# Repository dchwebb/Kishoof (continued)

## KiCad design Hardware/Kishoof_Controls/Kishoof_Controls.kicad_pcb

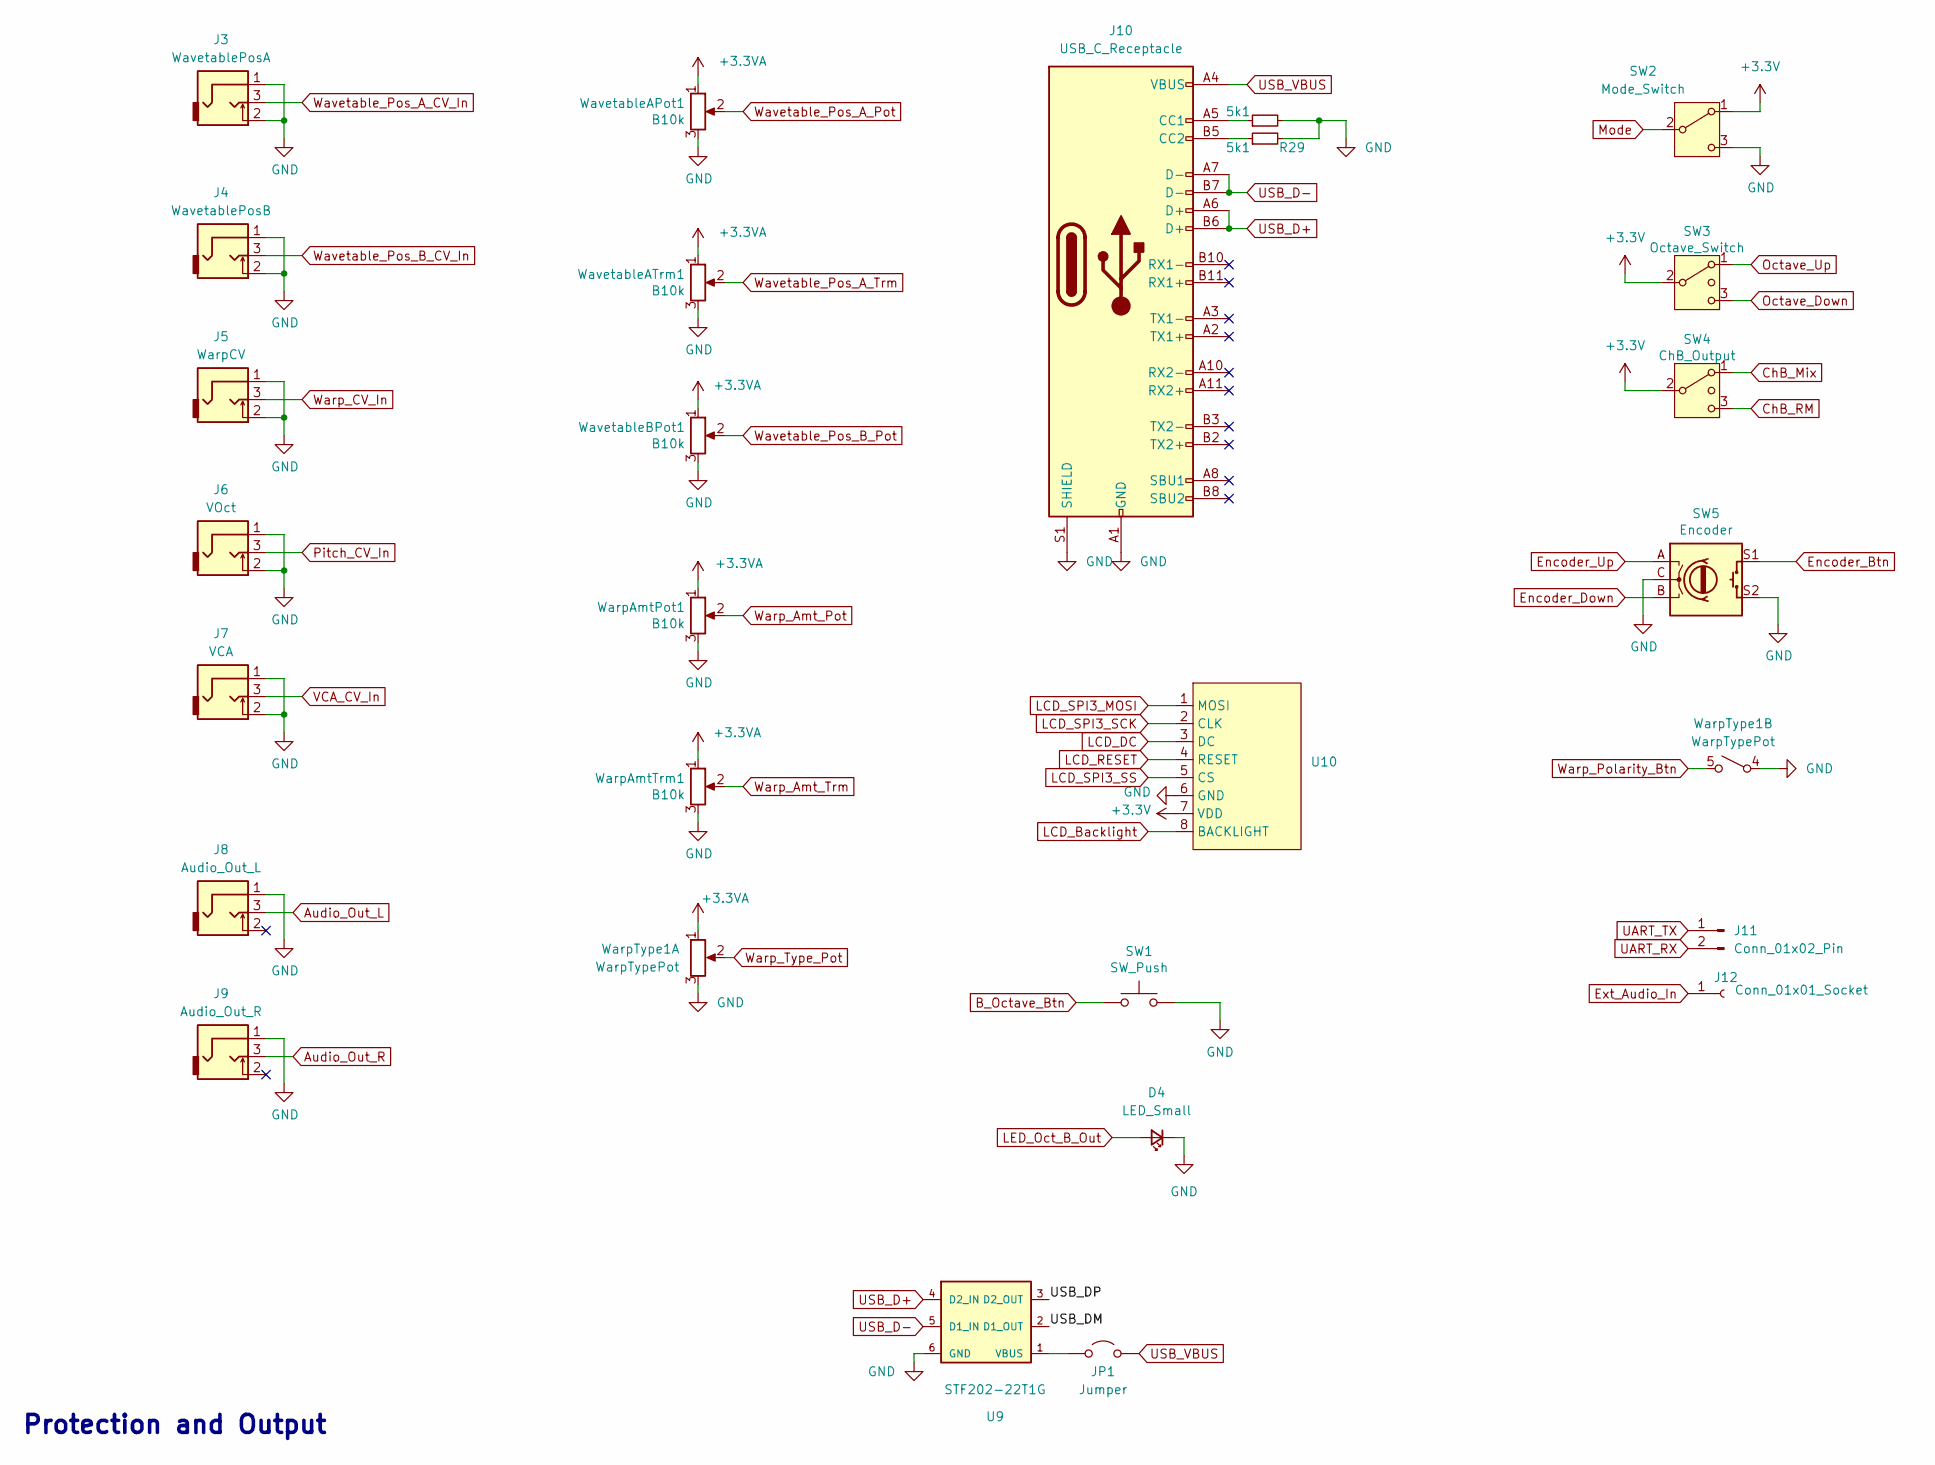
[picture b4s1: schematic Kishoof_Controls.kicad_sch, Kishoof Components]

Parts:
D4: LED_Small; LED_D3.0mm_FlatTop
J3: WavetablePosA; THONKICONN_hole
J4: WavetablePosB; THONKICONN_hole
J5: WarpCV; THONKICONN_hole
J6: VOct; THONKICONN_hole
J7: VCA; THONKICONN_hole
J8: Audio_Out_L; THONKICONN_hole
J9: Audio_Out_R; THONKICONN_hole
J10: USB_C_Receptacle; USB_C_Receptacle_Amphenol_12401951E412A
J11: Conn_01x02_Pin; PinHeader_1x02_P2.54mm_Vertical
J12: Conn_01x01_Socket; PinHeader_1x01_P2.54mm_Vertical
JP1: Jumper; SolderJumper-2_P1.3mm_Open_RoundedPad1.0x1.5mm
R28, R29: 5k1; R_0603_1608Metric; Part_Number C23186
SW1: SW_Push; SW_PUSH_6mm_aligned
SW2: Mode_Switch; SPDT_Miniature
SW3: Octave_Switch; SP3T_Mini_Switch
SW4: ChB_Output; SP3T_Mini_Switch
SW5: Encoder
U9: STF202-22T1G
U10: LCD_Riser
WarpAmtPot1: B10k; Alpha_9mm_Potentiometer_Aligned
WarpAmtTrm1: B10k; Alpha_9mm_Potentiometer_Aligned
WarpType1: WarpTypePot; Bourns_Switch_Potentiometer
WavetableAPot1: B10k; Alpha_9mm_Potentiometer_Aligned
WavetableATrm1: B10k; Alpha_9mm_Potentiometer_Aligned
WavetableBPot1: B10k; Alpha_9mm_Potentiometer_Aligned

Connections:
+3.3V: SW2.1 (A), SW3.2 (3), SW4.2 (3), U10.7 (VDD)
+3.3VA: WarpAmtPot1.1, WarpAmtTrm1.1, WarpType1.1, WavetableAPot1.1, WavetableATrm1.1, WavetableBPot1.1
/USB_DM: U9.2 (D1_OUT)
/USB_DP: U9.3 (D2_OUT)
Audio_Out_L: J8.3
Audio_Out_R: J9.3
B_Octave_Btn: SW1.1
ChB_Mix: SW4.1
ChB_RM: SW4.3 (4)
Encoder_Btn: SW5.S1
Encoder_Down: SW5.B
Encoder_Up: SW5.A
Ext_Audio_In: J12.1
GND: D4.1 (K), J3.1, J3.2, J4.1, J4.2, J5.1, J5.2, J6.1, J6.2, J7.1, J7.2, J8.1, J9.1, J10.A1 (GND), J10.A12 (GND), J10.B1 (GND), J10.B12 (GND), J10.S1 (SHIELD), R28.2, R29.2, SW1.2, SW2.3 (C), SW5.C, SW5.S2, U9.6 (GND), U10.6 (GND), WarpAmtPot1.3, WarpAmtTrm1.3, WarpType1.3, WarpType1.4 (1), WavetableAPot1.3, WavetableATrm1.3, WavetableBPot1.3
LCD_Backlight: U10.8 (BACKLIGHT)
LCD_DC: U10.3 (DC)
LCD_RESET: U10.4 (RESET)
LCD_SPI3_MOSI: U10.1 (MOSI)
LCD_SPI3_SCK: U10.2 (CLK)
LCD_SPI3_SS: U10.5 (CS)
LED_Oct_B_Out: D4.2 (A)
Mode: SW2.2 (B)
unnamed: J10.A5 (CC1), R28.1
unnamed: J10.B5 (CC2), R29.1
unnamed: JP1.1 (A), U9.1 (VBUS)
Octave_Down: SW3.3 (4)
Octave_Up: SW3.1
Pitch_CV_In: J6.3
UART_RX: J11.2
UART_TX: J11.1
USB_D+: J10.A6 (D+), J10.B6 (D+), U9.4 (D2_IN)
USB_D-: J10.A7 (D-), J10.B7 (D-), U9.5 (D1_IN)
USB_VBUS: J10.A4 (VBUS), J10.A9 (VBUS), J10.B4 (VBUS), J10.B9 (VBUS), JP1.2 (B)
VCA_CV_In: J7.3
Warp_Amt_Pot: WarpAmtPot1.2
Warp_Amt_Trm: WarpAmtTrm1.2
Warp_CV_In: J5.3
Warp_Polarity_Btn: WarpType1.5 (2)
Warp_Type_Pot: WarpType1.2
Wavetable_Pos_A_CV_In: J3.3
Wavetable_Pos_A_Pot: WavetableAPot1.2
Wavetable_Pos_A_Trm: WavetableATrm1.2
Wavetable_Pos_B_CV_In: J4.3
Wavetable_Pos_B_Pot: WavetableBPot1.2

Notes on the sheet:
Protection and Output

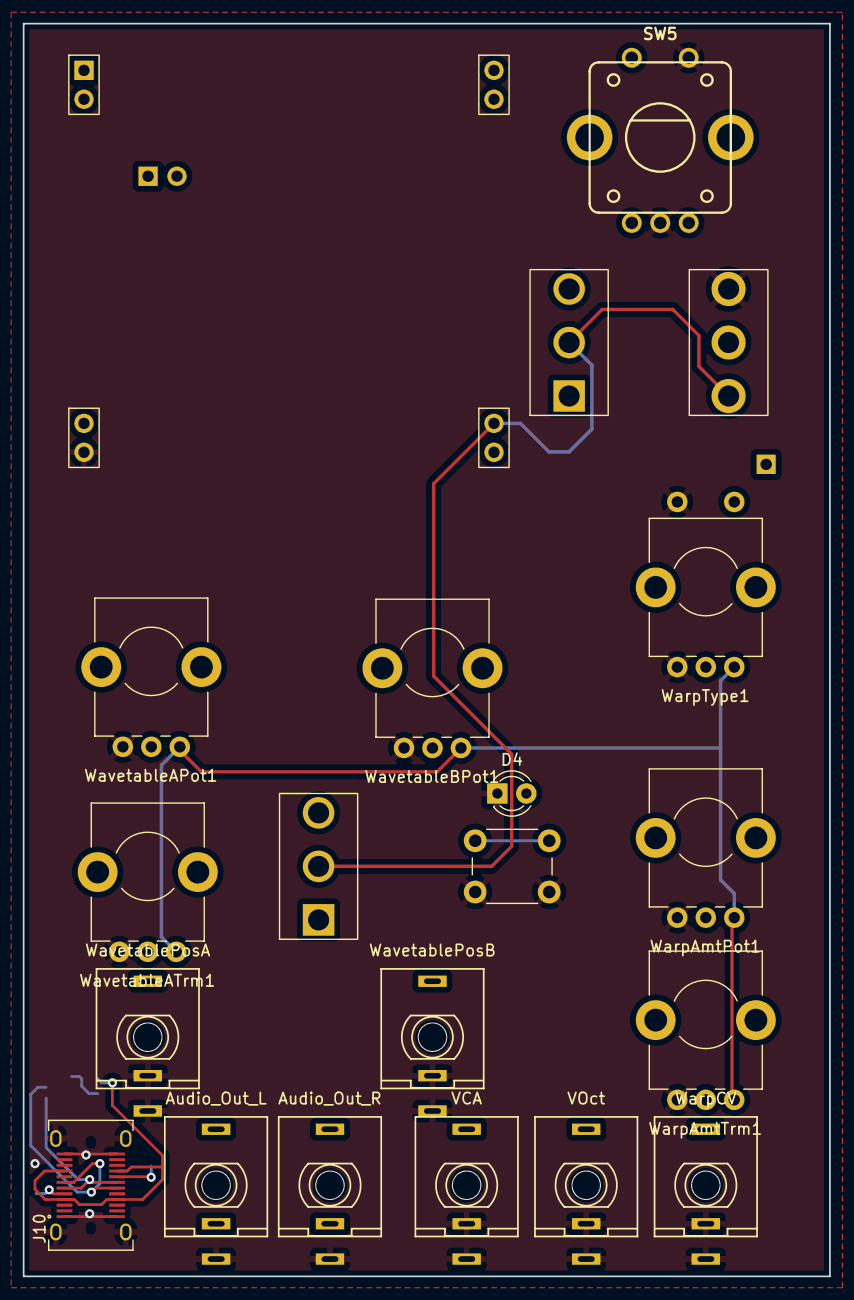
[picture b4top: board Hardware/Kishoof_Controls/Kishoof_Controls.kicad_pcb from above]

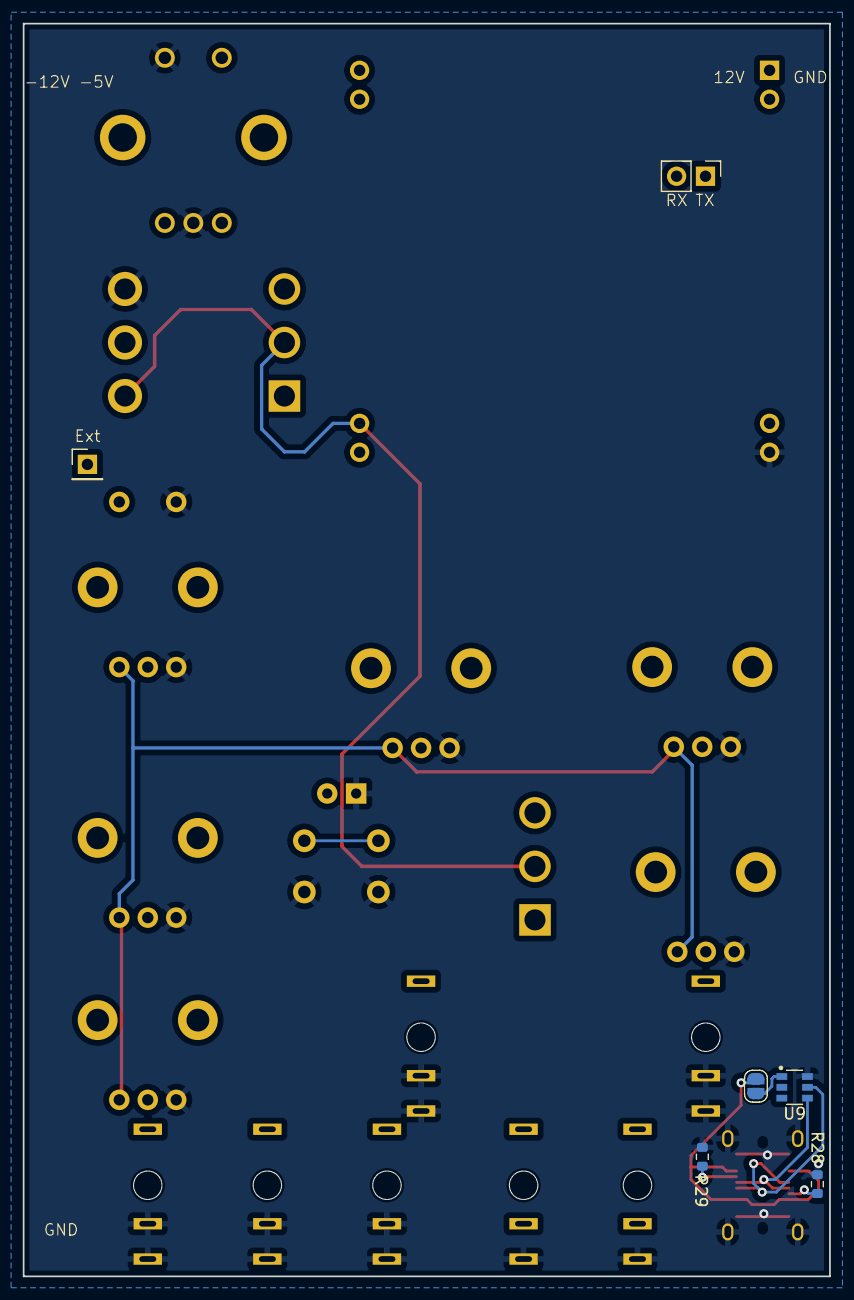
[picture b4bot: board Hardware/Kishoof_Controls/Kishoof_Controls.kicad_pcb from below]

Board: 4 copper layers, 70.8 x 110.0 mm, 27 parts (6 on the bottom side), 9 nets.

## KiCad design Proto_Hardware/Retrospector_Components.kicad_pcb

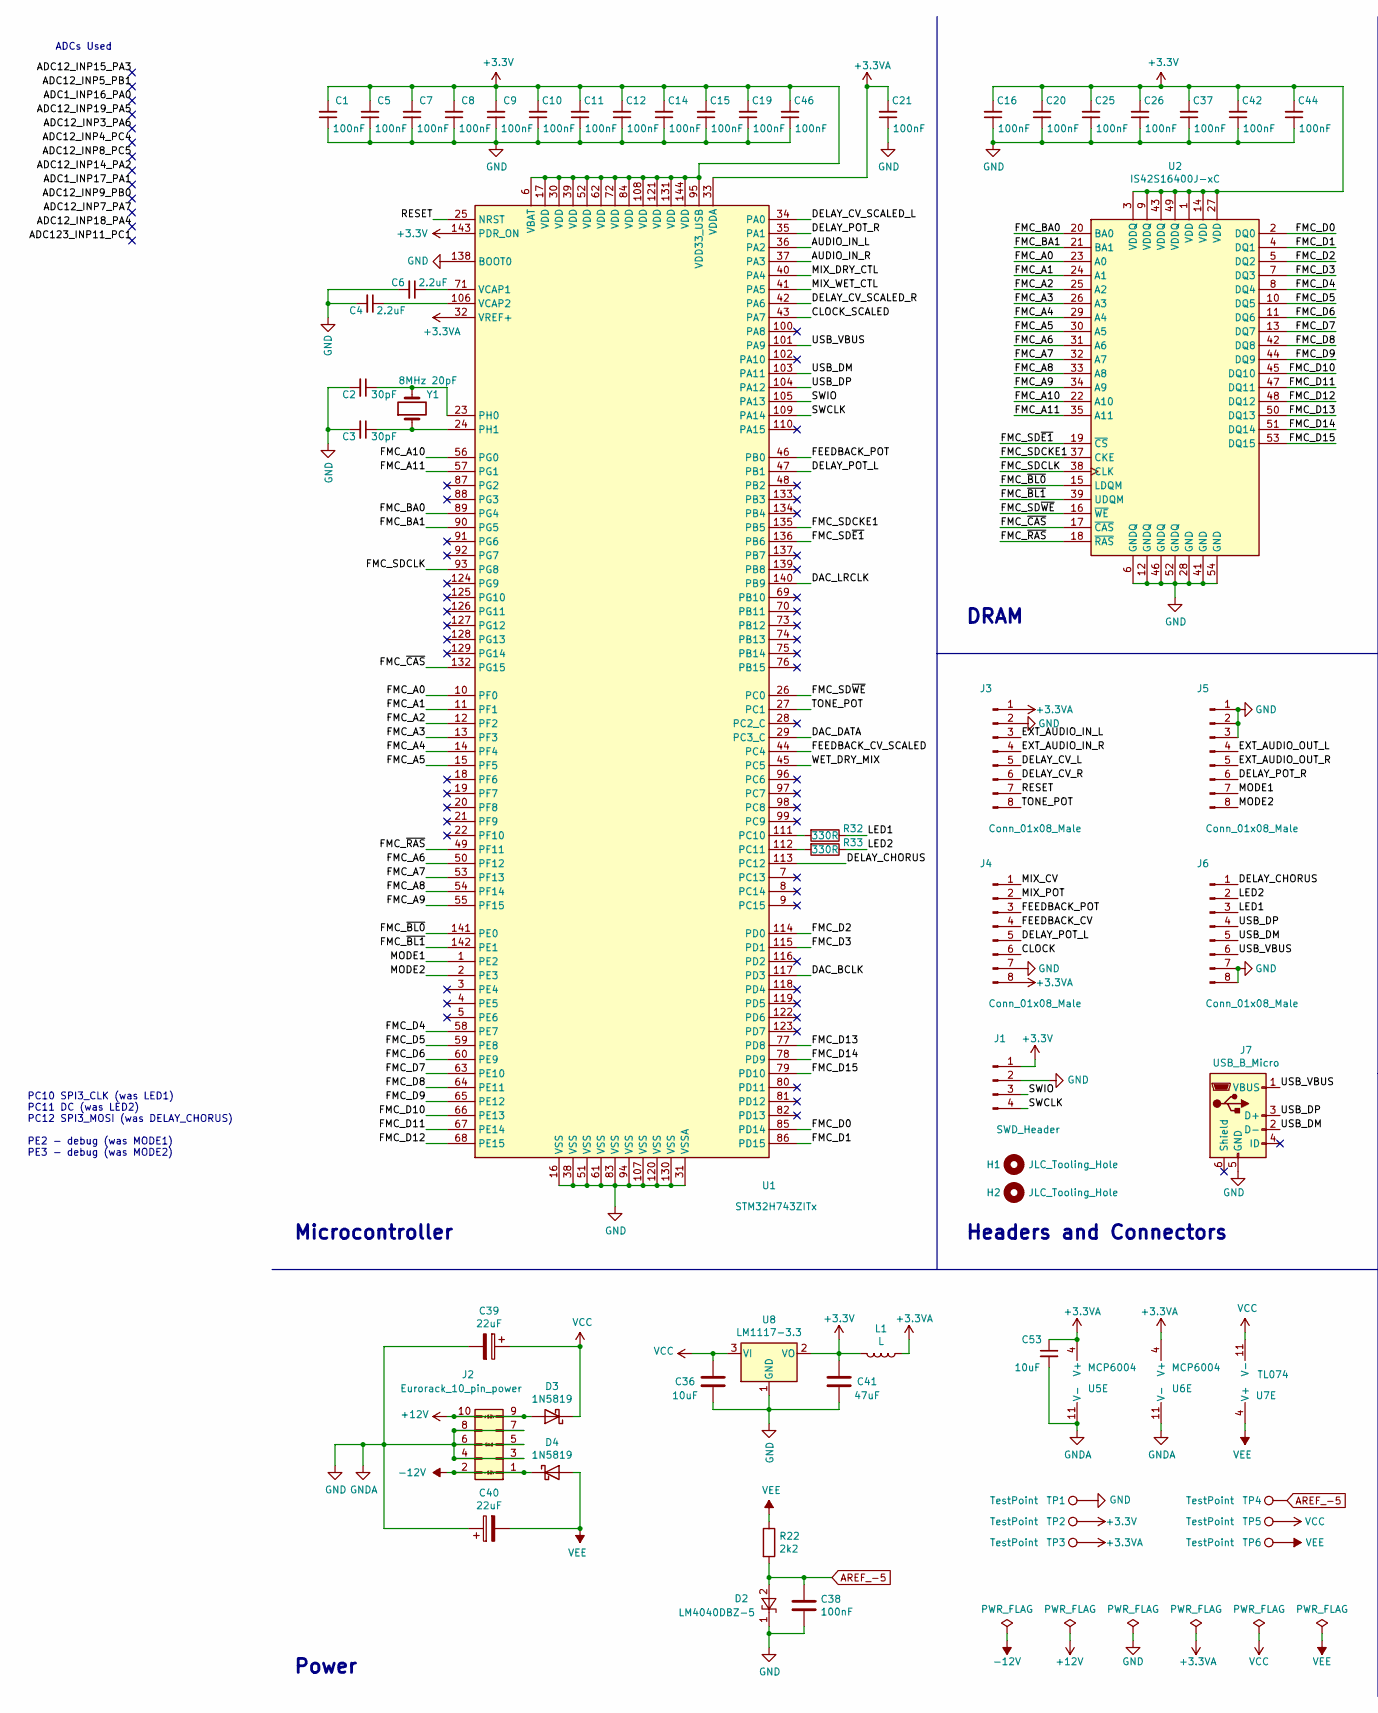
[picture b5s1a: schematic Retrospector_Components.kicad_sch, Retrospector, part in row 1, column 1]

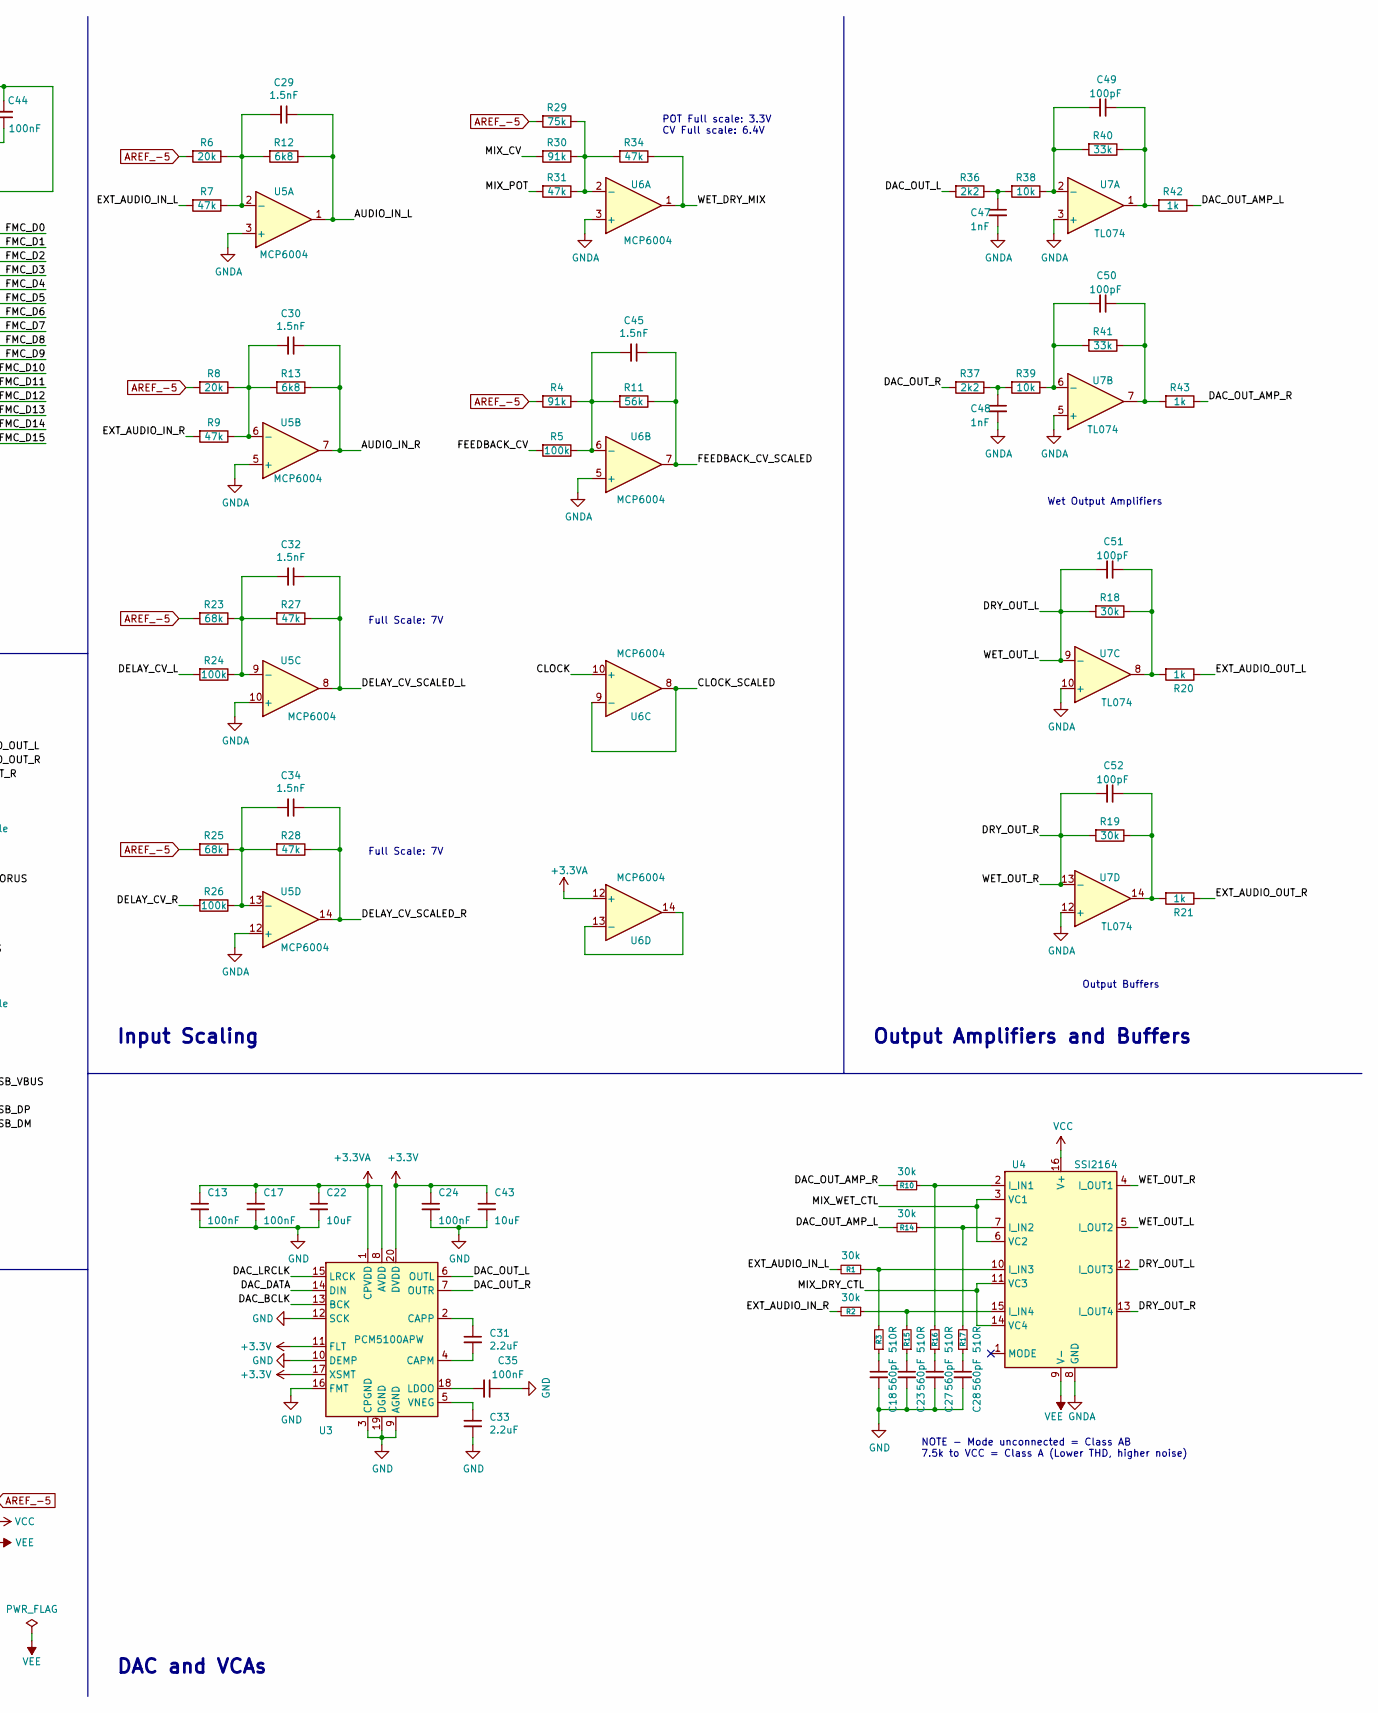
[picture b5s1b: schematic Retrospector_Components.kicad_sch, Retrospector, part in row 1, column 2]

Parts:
C1, C5, C7, C8, C9, C10, C11, C12, C13, C14, C15, C16, C17, C19, C20, C21, C24, C25, C26, C35, C37, C38, C42, C44, C46: 100nF; C_0603_HandSoldering; Part_Number C14663
C2, C3: 30pF; C_0603_HandSoldering; Part_Number C22397
C4, C6, C31, C33: 2.2uF; C_0603_HandSoldering; Part_Number C23630
C18, C23, C27, C28: 560pF; C_0603_HandSoldering; Part_Number C84721
C22, C43, C53: 10uF; C_0805; Part_Number C15850
C29, C30, C32, C34, C45: 1.5nF; C_0603_HandSoldering; Part_Number C1595
C36: 10uF; CP_Elec_3x5.3; Part_Number C249452
C39, C40: 22uF; CP_Elec_6.3x5.3; Part_Number C249771
C41: 47uF; CP_Elec_6.3x7.7; Part_Number C108053
C47, C48: 1nF; C_0805; Part_Number C46653
C49, C50, C51, C52: 100pF; C_0805; Part_Number C1790
D2: LM4040DBZ-5; SOT-23; Part_Number C69316
D3, D4: 1N5819; D_SOD-123; Part_Number C169540
H1, H2: JLC_Tooling_Hole; JLC_SMT_Tooling_Hole
J1: SWD_Header; SWD_header
J2: Eurorack_10_pin_power; Eurorack_10_pin_header
J3, J4, J5, J6: Conn_01x08_Male; Pin_Header_Straight_1x08_Pitch2.54mm
J7: USB_B_Micro; USB_Micro-B_Amphenol
L1: L; L_0805_HandSoldering; Part_Number C1046
R1, R2, R10, R14, R18, R19: 30k; R_0603_HandSoldering; Part_Number C22984
R3, R15, R16, R17: 510R; R_0603_HandSoldering; Part_Number C23193
R4, R30: 91k; R_0603_HandSoldering; Part_Number C23265
R5, R24, R26: 100k; R_0603_HandSoldering; Part_Number C25803
R6, R8: 20k; R_0603_HandSoldering; Part_Number C4184
R7, R9, R27, R28, R31, R34: 47k; R_0603_HandSoldering; Part_Number C25819
R11: 56k; R_0603_HandSoldering; Part_Number C23206
R12, R13: 6k8; R_0603_HandSoldering; Part_Number C23212
R20, R21, R42, R43: 1k; R_0603_HandSoldering; Part_Number C21190
R22, R36, R37: 2k2; R_0603_HandSoldering; Part_Number C4190
R23, R25: 68k; R_0603_HandSoldering; Part_Number C23231
R29: 75k; R_0603_HandSoldering; Part_Number C23242
R32, R33: 330R; R_0603_HandSoldering; Part_Number C23138
R38, R39: 10k; R_0603_HandSoldering; Part_Number C25804
R40, R41: 33k; R_0603_HandSoldering; Part_Number C4216
TP1, TP2, TP3, TP4, TP5, TP6: TestPoint; Test_Point_Keystone_5005-5009_Compact
U1: STM32H743ZITx; LQFP-144_20x20mm_P0.5mm; Part_Number C114408
U2: IS42S16400J-xC; TSOP-II-54_22.2x10.16mm_P0.8mm; Part_Number C69411
U3: PCM5100APW; SSOP-20_4.4x6.5mm_Pitch0.65mm_Round_Pads; Part_Number C131154
U4: SSI2164; SOIC-16_3.9x9.9mm_Pitch1.27mm
U5, U6: MCP6004; SOIC-14_N; Part_Number C7378
U7: TL074; SOIC-14_N; Part_Number C6964
U8: LM1117-3.3; SOT-223; Part_Number C6186
Y1: 8MHz 20pF; Crystal_SMD_5032-2pin_5.0x3.2mm_HandSoldering; Part_Number C115962

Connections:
+3.3VA: C13.1, C17.1, C21.2, C22.1, C53.1, J3.1, J4.8, L1.1, TP3.1, U1.32 (VREF+), U1.33 (VDDA), U3.1 (CPVDD), U3.8 (AVDD), U5.4 (V+), U6.4 (V+), U6.12 (+)
+3V3: C1.2, C5.2, C7.2, C8.2, C9.2, C10.2, C11.2, C12.2, C14.2, C15.2, C16.2, C19.2, C20.2, C24.1, C25.2, C26.2, C37.2, C41.1, C42.2, C43.1, C44.2, C46.2, J1.1, L1.2, TP2.1, U1.6 (VBAT), U1.17 (VDD), U1.30 (VDD), U1.39 (VDD), U1.52 (VDD), U1.62 (VDD), U1.72 (VDD), U1.84 (VDD), U1.95 (VDD33_USB), U1.108 (VDD), U1.121 (VDD), U1.131 (VDD), U1.143 (PDR_ON), U1.144 (VDD), U2.1 (VDD), U2.3 (VDDQ), U2.9 (VDDQ), U2.14 (VDD), U2.27 (VDD), U2.43 (VDDQ), U2.49 (VDDQ), U3.11 (FLT), U3.17 (XSMT), U3.20 (DVDD), U8.2 (VO)
+12V: D3.2 (A), J2.9, J2.10
-12V: D4.1 (K), J2.1, J2.2
/AUDIO_IN_L: C29.1, R12.1, U1.36 (PA2), U5.1
/AUDIO_IN_R: C30.1, R13.1, U1.37 (PA3), U5.7
/CLOCK: J4.6, U6.10 (+)
/CLOCK_SCALED: U1.43 (PA7), U6.8, U6.9 (-)
/DAC_BCLK: U1.117 (PD3), U3.13 (BCK)
/DAC_DATA: U1.29 (PC3_C), U3.14 (DIN)
/DAC_LRCLK: U1.140 (PB9), U3.15 (LRCK)
/DAC_OUT_AMP_L: R14.2, R42.1
/DAC_OUT_AMP_R: R10.2, R43.1
/DAC_OUT_L: R36.2, U3.6 (OUTL)
/DAC_OUT_R: R37.2, U3.7 (OUTR)
/DELAY_CHORUS: J6.1, U1.113 (PC12)
/DELAY_CV_L: J3.5, R24.2
/DELAY_CV_R: J3.6, R26.2
/DELAY_CV_SCALED_L: C32.1, R27.1, U1.34 (PA0), U5.8
/DELAY_CV_SCALED_R: C34.1, R28.1, U1.42 (PA6), U5.14
/DELAY_POT_L: J4.5, U1.47 (PB1)
/DELAY_POT_R: J5.6, U1.35 (PA1)
/DRY_OUT_L: C51.2, R18.2, U4.5 (I_OUT2), U4.12 (I_OUT3), U7.9 (-)
/DRY_OUT_R: C52.2, R19.2, U4.4 (I_OUT1), U4.13 (I_OUT4), U7.13 (-)
/EXT_AUDIO_IN_L: J3.3, R1.2, R7.2
/EXT_AUDIO_IN_R: J3.4, R2.2, R9.2
/EXT_AUDIO_OUT_L: J5.4, R20.1
/EXT_AUDIO_OUT_R: J5.5, R21.1
/FEEDBACK_CV: J4.4, R5.2
/FEEDBACK_CV_SCALED: C45.1, R11.1, U1.44 (PC4), U6.7
/FEEDBACK_POT: J4.3, U1.46 (PB0)
/FMC_A0: U1.10 (PF0), U2.23 (A0)
/FMC_A1: U1.11 (PF1), U2.24 (A1)
/FMC_A2: U1.12 (PF2), U2.25 (A2)
/FMC_A3: U1.13 (PF3), U2.26 (A3)
/FMC_A4: U1.14 (PF4), U2.29 (A4)
/FMC_A5: U1.15 (PF5), U2.30 (A5)
/FMC_A6: U1.50 (PF12), U2.31 (A6)
/FMC_A7: U1.53 (PF13), U2.32 (A7)
/FMC_A8: U1.54 (PF14), U2.33 (A8)
/FMC_A9: U1.55 (PF15), U2.34 (A9)
/FMC_A10: U1.56 (PG0), U2.22 (A10)
/FMC_A11: U1.57 (PG1), U2.35 (A11)
/FMC_BA0: U1.89 (PG4), U2.20 (BA0)
/FMC_BA1: U1.90 (PG5), U2.21 (BA1)
/FMC_D0: U1.85 (PD14), U2.2 (DQ0)
/FMC_D1: U1.86 (PD15), U2.4 (DQ1)
/FMC_D2: U1.114 (PD0), U2.5 (DQ2)
/FMC_D3: U1.115 (PD1), U2.7 (DQ3)
/FMC_D4: U1.58 (PE7), U2.8 (DQ4)
/FMC_D5: U1.59 (PE8), U2.10 (DQ5)
/FMC_D6: U1.60 (PE9), U2.11 (DQ6)
/FMC_D7: U1.63 (PE10), U2.13 (DQ7)
/FMC_D8: U1.64 (PE11), U2.42 (DQ8)
/FMC_D9: U1.65 (PE12), U2.44 (DQ9)
/FMC_D10: U1.66 (PE13), U2.45 (DQ10)
/FMC_D11: U1.67 (PE14), U2.47 (DQ11)
/FMC_D12: U1.68 (PE15), U2.48 (DQ12)
/FMC_D13: U1.77 (PD8), U2.50 (DQ13)
/FMC_D14: U1.78 (PD9), U2.51 (DQ14)
/FMC_D15: U1.79 (PD10), U2.53 (DQ15)
/FMC_SDCKE1: U1.135 (PB5), U2.37 (CKE)
/FMC_SDCLK: U1.93 (PG8), U2.38 (CLK)
/FMC_SD~E1: U1.136 (PB6), U2.19 (~CS)
/FMC_SD~WE: U1.26 (PC0), U2.16 (~WE)
/FMC_~BL0: U1.141 (PE0), U2.15 (LDQM)
/FMC_~BL1: U1.142 (PE1), U2.39 (UDQM)
/FMC_~CAS: U1.132 (PG15), U2.17 (~CAS)
/FMC_~RAS: U1.49 (PF11), U2.18 (~RAS)
/LED1: J6.3, R32.1
/LED2: J6.2, R33.1
/MIX_CV: J4.1, R30.2
/MIX_DRY_CTL: U1.40 (PA4), U4.11 (VC3), U4.14 (VC4)
/MIX_POT: J4.2, R31.2
/MIX_WET_CTL: U1.41 (PA5), U4.3 (VC1), U4.6 (VC2)
/MODE1: J5.7, U1.1 (PE2)
/MODE2: J5.8, U1.2 (PE3)
/RESET: J3.7, U1.25 (NRST)
/SWCLK: J1.4, U1.109 (PA14)
/SWIO: J1.3, U1.105 (PA13)
/TONE_POT: J3.8, U1.27 (PC1)
/USB_DM: J6.5, J7.2 (D-), U1.103 (PA11)
/USB_DP: J6.4, J7.3 (D+), U1.104 (PA12)
/USB_VBUS: J6.6, J7.1 (VBUS), U1.101 (PA9)
/WET_DRY_MIX: R34.1, U1.45 (PC5), U6.1
AREF_-5: C38.1, D2.2 (A), R4.2, R6.2, R8.2, R22.2, R23.2, R25.2, R29.2, TP4.1
GND: C1.1, C2.2, C3.2, C4.2, C5.1, C6.2, C7.1, C8.1, C9.1, C10.1, C11.1, C12.1, C13.2, C14.1, C15.1, C16.1, C17.2, C18.2, C19.1, C20.1, C21.1, C22.2, C23.2, C24.2, C25.1, C26.1, C27.2, C28.2, C33.2, C35.1, C36.2, C37.1, C38.2, C39.2, C40.1, C41.2, C42.1, C43.2, C44.1, C46.1, C47.2, C48.2, C53.2, D2.1 (K), J1.2, J2.3, J2.4, J2.5, J2.6, J2.7, J2.8, J3.2, J4.7, J5.1, J5.2, J5.3, J6.7, J6.8, J7.5 (GND), TP1.1, U1.16 (VSS), U1.31 (VSSA), U1.38 (VSS), U1.51 (VSS), U1.61 (VSS), U1.83 (VSS), U1.94 (VSS), U1.107 (VSS), U1.120 (VSS), U1.130 (VSS), U1.138 (BOOT0), U2.6 (GNDQ), U2.12 (GNDQ), U2.28 (GND), U2.41 (GND), U2.46 (GNDQ), U2.52 (GNDQ), U2.54 (GND), U3.3 (CPGND), U3.9 (AGND)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
unnamed: C2.1, U1.23 (PH0), Y1.2
unnamed: C3.1, U1.24 (PH1), Y1.1
unnamed: C4.1, U1.106 (VCAP2)
unnamed: C6.1, U1.71 (VCAP1)
unnamed: C18.1, R3.1
unnamed: C23.1, R15.1
unnamed: C27.1, R16.1
unnamed: C28.1, R17.1
unnamed: C29.2, R6.1, R7.1, R12.2, U5.2 (-)
unnamed: C30.2, R8.1, R9.1, R13.2, U5.6 (-)
unnamed: C31.1, U3.2 (CAPP)
unnamed: C31.2, U3.4 (CAPM)
unnamed: C32.2, R23.1, R24.1, R27.2, U5.9 (-)
unnamed: C33.1, U3.5 (VNEG)
unnamed: C34.2, R25.1, R26.1, R28.2, U5.13 (-)
unnamed: C35.2, U3.18 (LDOO)
unnamed: C45.2, R4.1, R5.1, R11.2, U6.6 (-)
unnamed: C47.1, R36.1, R38.2
unnamed: C48.1, R37.1, R39.2
unnamed: C49.1, R40.1, R42.2, U7.1
unnamed: C49.2, R38.1, R40.2, U7.2 (-)
unnamed: C50.1, R41.1, R43.2, U7.7
unnamed: C50.2, R39.1, R41.2, U7.6 (-)
unnamed: C51.1, R18.1, R20.2, U7.8
unnamed: C52.1, R19.1, R21.2, U7.14
unnamed: R1.1, R3.2, U4.10 (I_IN3)
unnamed: R10.1, R16.2, U4.2 (I_IN1)
unnamed: R14.1, R17.2, U4.7 (I_IN2)
unnamed: R2.1, R15.2, U4.15 (I_IN4)
unnamed: R29.1, R30.1, R31.1, R34.2, U6.2 (-)
unnamed: R32.2, U1.111 (PC10)
unnamed: R33.2, U1.112 (PC11)
unnamed: U6.13 (-), U6.14
VCC: C36.1, C39.1, D3.1 (K), TP5.1, U4.16 (V+), U7.11 (V-), U8.3 (VI)
VEE: C40.2, D4.2 (A), R22.1, TP6.1, U4.9 (V-), U7.4 (V+)

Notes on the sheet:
DAC and VCAs
NOTE - Mode unconnected = Class AB 7.5k to VCC = Class A (Lower THD, higher noise)
Input Scaling
Output Buffers
ADCs Used
Full Scale: 7V
Wet Output Amplifiers
Output Amplifiers and Buffers
POT Full scale: 3.3V CV Full scale: 6.4V
Power
PC10 SPI3_CLK (was LED1) PC11 DC (was LED2) PC12 SPI3_MOSI (was DELAY_CHORUS) PE2 - debug (was MODE1) PE3 - debug (was MODE2)
Microcontroller
Headers and Connectors
DRAM

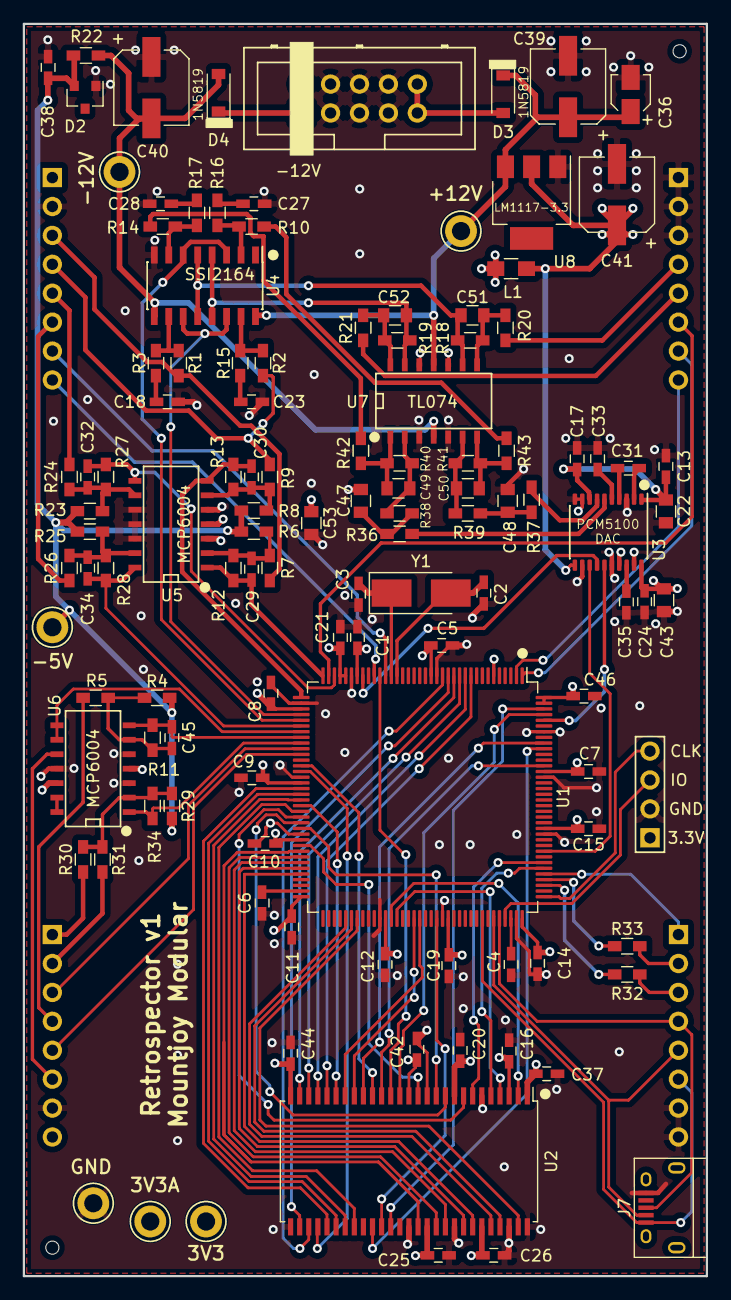
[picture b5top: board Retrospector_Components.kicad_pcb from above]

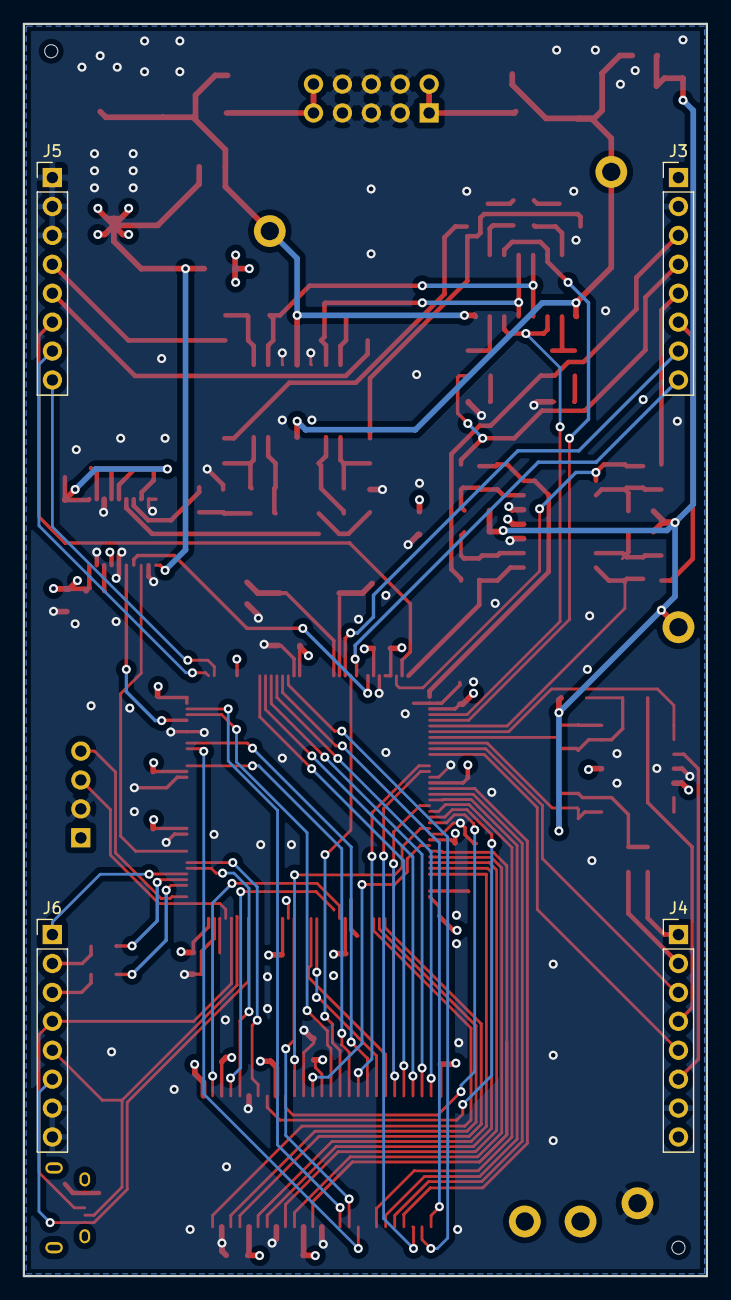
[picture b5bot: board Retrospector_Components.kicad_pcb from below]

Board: 4 copper layers, 60.0 x 110.0 mm, 123 parts (4 on the bottom side), 122 nets.

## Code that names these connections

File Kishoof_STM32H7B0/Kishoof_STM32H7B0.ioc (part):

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Mcu.Name=STM32H7B0VBTx
Mcu.Package=LQFP100
Mcu.UserName=STM32H7B0VBTx
PA0.Mode=IN16-Single-Ended
PA0.Signal=ADC1_INP16
PA1.Mode=IN17-Single-Ended
PA1.Signal=ADC1_INP17
PA11.Mode=Host_FS
PA11.Signal=USB_OTG_HS_DM
PA12.Mode=Host_FS
PA12.Signal=USB_OTG_HS_DP
PA15.Mode=NSS_Signal_Hard_Output
PA15.Signal=SPI3_NSS
PA2.Signal=ADCx_INP14
PA3.Mode=IN15-Single-Ended
PA3.Signal=ADC1_INP15
PA4.Signal=ADCx_INP18
PA5.Signal=ADCx_INP19
PA6.Signal=ADCx_INP3
PA7.Signal=ADCx_INP7
PA9.Mode=Activate_VBUS_FS
PA9.Signal=USB_OTG_HS_VBUS
PB0.Signal=ADCx_INP9
PB1.Signal=ADCx_INP5
PB12.Mode=Half_Duplex_Master_Tx
PB12.Signal=I2S2_WS
PB13.Mode=Half_Duplex_Master_Tx
PB13.Signal=I2S2_CK
PB15.Mode=Half_Duplex_Master_Tx
PB15.Signal=I2S2_SDO
PB2.Mode=O1_P1_CLK
PB2.Signal=OCTOSPIM_P1_CLK
PB6.GPIOParameters=GPIO_Label
PB6.GPIO_Label=LCD_DC
PB6.Signal=GPIO_Input
PB7.GPIOParameters=GPIO_Label
PB7.GPIO_Label=LCD_RESET
PB7.Signal=GPIO_Input
PC0.Signal=ADCx_INP10
PC1.Signal=ADCx_INP11
PC10.Mode=TX_Only_Simplex_Unidirect_Master
PC10.Signal=SPI3_SCK
PC12.Mode=TX_Only_Simplex_Unidirect_Master
PC12.Signal=SPI3_MOSI
PC2_C.Mode=OCTOSPI1_IOL_Port1L
PC2_C.Signal=OCTOSPIM_P1_IO2
PC5.Mode=OCTOSPI1_Port1_DQS
PC5.Signal=OCTOSPIM_P1_DQS
PC6.Signal=S_TIM3_CH1
PC7.Signal=S_TIM3_CH2
PC9.Mode=OCTOSPI1_IOL_Port1L
PC9.Signal=OCTOSPIM_P1_IO0
PD0.GPIOParameters=GPIO_Label
PD0.GPIO_Label=Octave_Up
PD0.Signal=GPIO_Input
PD1.GPIOParameters=GPIO_Label
PD1.GPIO_Label=Octave_Down
PD1.Signal=GPIO_Input
PD10.GPIOParameters=GPIO_Label
PD10.GPIO_Label=B_Octave_Btn
PD10.Signal=GPIO_Input
PD12.Mode=OCTOSPI1_IOL_Port1L
PD12.Signal=OCTOSPIM_P1_IO1
PD13.Mode=OCTOSPI1_IOL_Port1L
PD13.Signal=OCTOSPIM_P1_IO3
PD14.Signal=S_TIM4_CH3
PD5.Mode=Asynchronous
PD5.Signal=USART2_TX
PD6.Mode=Asynchronous
PD6.Signal=USART2_RX
PD8.GPIOParameters=GPIO_Label
PD8.GPIO_Label=ChB_Mix
PD8.Signal=GPIO_Input
PD9.GPIOParameters=GPIO_Label
PD9.GPIO_Label=ChB_RM
PD9.Signal=GPIO_Input
PE10.Mode=OCTOSPI1_IOH_Port1H
PE10.Signal=OCTOSPIM_P1_IO7
PE11.Mode=OCTOSPI1_Port1_NCS
PE11.Signal=OCTOSPIM_P1_NCS
PE2.GPIOParameters=GPIO_Label
PE2.GPIO_Label=Mode
PE2.Signal=GPIO_Input
PE3.GPIOParameters=GPIO_Label
PE3.GPIO_Label=Warp_Polarity_Btn
PE3.Signal=GPIO_Input
PE4.GPIOParameters=GPIO_Label
PE4.GPIO_Label=ENCODER_BTN
PE4.Signal=GPIO_Input
PE7.Mode=OCTOSPI1_IOH_Port1H
PE7.Signal=OCTOSPIM_P1_IO4
PE8.Mode=OCTOSPI1_IOH_Port1H
PE8.Signal=OCTOSPIM_P1_IO5
PE9.Mode=OCTOSPI1_IOH_Port1H
PE9.Signal=OCTOSPIM_P1_IO6
PH0-OSC_IN.Mode=HSE-External-Oscillator
PH0-OSC_IN.Signal=RCC_OSC_IN
PH1-OSC_OUT.Mode=HSE-External-Oscillator
PH1-OSC_OUT.Signal=RCC_OSC_OUT
RCC.HSE_VALUE=8000000
RCC.SYSCLKFreq_VALUE=280000000
RCC.SYSCLKSource=RCC_SYSCLKSOURCE_PLLCLK
board=custom

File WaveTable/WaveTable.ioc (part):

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Mcu.Name=STM32H743ZITx
Mcu.Package=LQFP144
Mcu.UserName=STM32H743ZITx
PA11.Mode=Device_Only
PA11.Signal=USB_OTG_FS_DM
PA12.Mode=Device_Only
PA12.Signal=USB_OTG_FS_DP
PA4.Signal=ADCx_INP18
PA5.Signal=COMP_DAC12_group
PA7.Signal=FMC_SDNWE
PA8.Mode=Activate_SOF_FS
PA8.Signal=USB_OTG_FS_SOF
PA9.Mode=Activate_VBUS
PA9.Signal=USB_OTG_FS_VBUS
PB0.GPIOParameters=GPIO_Label
PB0.GPIO_Label=LD1 [Green Led]
PB0.Signal=GPIO_Output
PB13.Mode=Half_Duplex_Master_Tx
PB13.Signal=I2S2_CK
PB14.GPIOParameters=GPIO_Label
PB14.GPIO_Label=LD3 [Red Led]
PB14.Signal=GPIO_Output
PB15.Mode=Half_Duplex_Master_Tx
PB15.Signal=I2S2_SDO
PB5.Mode=SdramChipSelect2_2
PB5.Signal=FMC_SDCKE1
PB6.Mode=SdramChipSelect2_2
PB6.Signal=FMC_SDNE1
PB7.GPIOParameters=GPIO_Pu
PB7.GPIO_Pu=GPIO_PULLUP
PB7.Mode=I2C
PB7.Signal=I2C1_SDA
PB8.GPIOParameters=GPIO_Pu
PB8.GPIO_Pu=GPIO_PULLUP
PB8.Mode=I2C
PB8.Signal=I2C1_SCL
PB9.Mode=Half_Duplex_Master_Tx
PB9.Signal=I2S2_WS
PC0.Signal=ADCx_INP10
PC13.GPIOParameters=GPIO_Label
PC13.GPIO_Label=B1 [Blue PushButton]
PC13.Signal=GPIO_Input
PC14-OSC32_IN\ (OSC32_IN).Mode=LSE-External-Oscillator
PC14-OSC32_IN\ (OSC32_IN).Signal=RCC_OSC32_IN
PC15-OSC32_OUT\ (OSC32_OUT).Mode=LSE-External-Oscillator
PC15-OSC32_OUT\ (OSC32_OUT).Signal=RCC_OSC32_OUT
PD0.Signal=FMC_D2_DA2
PD1.Signal=FMC_D3_DA3
PD10.Signal=FMC_D15_DA15
PD14.Signal=FMC_D0_DA0
PD15.Signal=FMC_D1_DA1
PD8.Signal=FMC_D13_DA13
PD9.Signal=FMC_D14_DA14
PE0.Signal=FMC_NBL0
PE1.Signal=FMC_NBL1
PE10.Signal=FMC_D7_DA7
PE11.Signal=FMC_D8_DA8
PE12.Signal=FMC_D9_DA9
PE13.Signal=FMC_D10_DA10
PE14.Signal=FMC_D11_DA11
PE15.Signal=FMC_D12_DA12
PE7.Signal=FMC_D4_DA4
PE8.Signal=FMC_D5_DA5
PE9.Signal=FMC_D6_DA6
PF0.Signal=FMC_A0
PF1.Signal=FMC_A1
PF11.Signal=FMC_SDNRAS
PF12.Signal=FMC_A6
PF13.Signal=FMC_A7
PF14.Signal=FMC_A8
PF15.Signal=FMC_A9
PF2.Signal=FMC_A2
PF3.Signal=FMC_A3
PF4.Signal=FMC_A4
PF5.Signal=FMC_A5
PF7.Mode=TX_Only_Simplex_Unidirect_Master
PF7.Signal=SPI5_SCK
PF9.Mode=TX_Only_Simplex_Unidirect_Master
PF9.Signal=SPI5_MOSI
PG0.Signal=FMC_A10
PG1.Signal=FMC_A11
PG15.Signal=FMC_SDNCAS
PG2.Signal=FMC_A12
PG4.Signal=FMC_A14_BA0
PG5.Signal=FMC_A15_BA1
PG7.GPIOParameters=GPIO_Label
PG7.GPIO_Label=USB_OTG_FS_OVCR
PG7.Signal=GPXTI7
PG8.Signal=FMC_SDCLK
PH0-OSC_IN\ (PH0).Mode=HSE-External-Oscillator
PH0-OSC_IN\ (PH0).Signal=RCC_OSC_IN
PH1-OSC_OUT\ (PH1).Mode=HSE-External-Oscillator
PH1-OSC_OUT\ (PH1).Signal=RCC_OSC_OUT
RCC.HSE_VALUE=8000000
RCC.SYSCLKFreq_VALUE=400000000
RCC.SYSCLKSource=RCC_SYSCLKSOURCE_PLLCLK
board=NUCLEO-H743ZI2
boardIOC=true

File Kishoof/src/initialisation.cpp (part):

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#include "initialisation.h"
#include "Calib.h"

GpioPin debugPin1	{GPIOD, 6, GpioPin::Type::Output};			// PD5: Debug
GpioPin debugPin2	{GPIOD, 5, GpioPin::Type::Output};			// PD6: Debug

// Clock overview:
// I2S 				PLL2 P 				61.44 MHz
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	// Maximum frequency should be 100MHz - see GC9A01 manual p. 189
	RCC->APB1LENR |= RCC_APB1LENR_SPI3EN;

	GpioPin::Init(GPIOC, 10, GpioPin::Type::AlternateFunction, 6, GpioPin::DriveStrength::High);		// PC10: SPI3_SCK AF6
	GpioPin::Init(GPIOC, 12, GpioPin::Type::AlternateFunction, 6, GpioPin::DriveStrength::High);		// PC12: SPI3_MOSI AF6
	//GpioPin::Init(GPIOA, 15, GpioPin::Type::AlternateFunction, 6, GpioPin::DriveStrength::High);			// PA15: SPI3_SS AF6

	// Configure SPI
	SPI3->CFG2 |= SPI_CFG2_COMM_0;					// 00: full-duplex, *01: simplex transmitter, 10: simplex receiver, 11: half-duplex
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
/*-----------------------------------------------------------------------------------------------------------------
ADC1:
	PA0 ADC1_INP16 Wavetable_Pos_B_Pot
	PA1 ADC1_INP17 Wavetable_Pos_A_Trm
	PA2 ADC1_INP14 AudioIn
	PA3 ADC1_INP15 WarpCV
	PA4 ADC1_INP18 Pitch_CV_Scaled
	PA5 ADC1_INP19 WavetablePosB_CV
ADC2:
	PA6 ADC12_INP3 VcaCV
	PA7 ADC12_INP7 WavetablePosA_CV
	PB0 ADC12_INP9 Warp_Type_Pot
	PB1 ADC12_INP5 Wavetable_Pos_A_Pot
	PC0 ADC12_INP10 Warp_Amt_Trm
	PC1	ADC12_INP11	Warp_Amt_Pot
*/

void InitADC1()
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
	/*--------------------------------------------------------------------------------------------
	Configure ADC Channels to be converted:
	PA0 ADC1_INP16 Wavetable_Pos_B_Pot
	PA1 ADC1_INP17 Wavetable_Pos_A_Trm
	PA2 ADC1_INP14 AudioIn
	PA3 ADC1_INP15 WarpCV
	PA4 ADC1_INP18 Pitch_CV_Scaled
	PA5 ADC1_INP19 WavetablePosB_CV
	*/
	InitAdcPins(ADC1, {16, 17, 14, 15, 18, 19});

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	while ((ADC2->CR & ADC_CR_ADCAL) == ADC_CR_ADCAL) {};

	/* Configure ADC Channels to be converted:
	PA6 ADC12_INP3 VcaCV
	PA7 ADC12_INP7 WavetablePosA_CV
	PB0 ADC12_INP9 Warp_Type_Pot
	PB1 ADC12_INP5 Wavetable_Pos_A_Pot
	PC0 ADC12_INP10 Warp_Amt_Trm
	PC1	ADC12_INP11	Warp_Amt_Pot
	*/
	InitAdcPins(ADC2, {3, 7, 9, 5, 10, 11});

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{
	RCC->APB1LENR |= RCC_APB1LENR_SPI2EN;			//	Enable SPI clocks

	GpioPin::Init(GPIOB, 12, GpioPin::Type::AlternateFunction, 5);		// PB12: I2S2_WS [alternate function AF5]
	GpioPin::Init(GPIOB, 13, GpioPin::Type::AlternateFunction, 5);		// PB13: I2S2_CK [alternate function AF5]
	GpioPin::Init(GPIOB, 15, GpioPin::Type::AlternateFunction, 5);		// PB15: I2S2_SDO [alternate function AF5]

	// Configure SPI (Shown as SPI2->CGFR in SFR)
	SPI2->I2SCFGR |= SPI_I2SCFGR_I2SMOD;			// I2S Mode
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
void InitEncoders()
{
	// Encoder: button on PE4, up/down on PC6 and PC7
	GpioPin::Init(GPIOE, 4, GpioPin::Type::InputPullup);				// PE4: Button
	GpioPin::Init(GPIOC, 6, GpioPin::Type::AlternateFunction, 3);		// PC6: TIM8_CH1 AF3
	GpioPin::Init(GPIOC, 7, GpioPin::Type::AlternateFunction, 3);		// PC7: TIM8_CH2 AF3

	RCC->APB4ENR |= RCC_APB4ENR_SYSCFGEN;			// Enable system configuration clock: used to manage external interrupt line connection to GPIOs
	// Encoder using timer functionality - PC6 and PC7
	GPIOC->PUPDR |= GPIO_PUPDR_PUPD6_0 |			// Set encoder pins to pull up
					GPIO_PUPDR_PUPD7_0;

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
void InitOctoSPI()
{
	GpioPin::Init(GPIOB, 2, GpioPin::Type::AlternateFunction, 9, GpioPin::DriveStrength::VeryHigh);		// PB2  OCTOSPI_CLK AF9
	GpioPin::Init(GPIOC, 9, GpioPin::Type::AlternateFunction, 9, GpioPin::DriveStrength::VeryHigh);		// PC9  OCTOSPI_IO0 AF9
	GpioPin::Init(GPIOD, 12, GpioPin::Type::AlternateFunction, 9, GpioPin::DriveStrength::VeryHigh);	// PD12 OCTOSPI_IO1 AF9
	GpioPin::Init(GPIOC, 2, GpioPin::Type::AlternateFunction, 9, GpioPin::DriveStrength::VeryHigh);		// PC2  OCTOSPI_IO2 AF9
	GpioPin::Init(GPIOD, 13, GpioPin::Type::AlternateFunction, 9, GpioPin::DriveStrength::VeryHigh);	// PD13 OCTOSPI_IO3 AF9
	GpioPin::Init(GPIOE, 7, GpioPin::Type::AlternateFunction, 10, GpioPin::DriveStrength::VeryHigh); 	// PE7  OCTOSPI_IO4 AF10
	GpioPin::Init(GPIOE, 8, GpioPin::Type::AlternateFunction, 10, GpioPin::DriveStrength::VeryHigh); 	// PE8  OCTOSPI_IO5 AF10
	GpioPin::Init(GPIOE, 9, GpioPin::Type::AlternateFunction, 10, GpioPin::DriveStrength::VeryHigh);	// PE9  OCTOSPI_IO6 AF10
	GpioPin::Init(GPIOE, 10, GpioPin::Type::AlternateFunction, 10, GpioPin::DriveStrength::VeryHigh);	// PE10 OCTOSPI_IO7 AF10
	GpioPin::Init(GPIOE, 11, GpioPin::Type::AlternateFunction, 11, GpioPin::DriveStrength::VeryHigh);	// PE11 OCTOSPI_NCS AF11
	GpioPin::Init(GPIOC, 5, GpioPin::Type::AlternateFunction, 10, GpioPin::DriveStrength::VeryHigh);	// PC5  OCTOSPI_DQS AF10

	RCC->AHB3ENR |= RCC_AHB3ENR_OSPI1EN;
	RCC->CDCCIPR |= RCC_CDCCIPR_OCTOSPISEL_1;				// kernel clock 100MHz: 00 rcc_hclk3; 01 pll1_q_ck; *10 pll2_r_ck; 11 per_ck
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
